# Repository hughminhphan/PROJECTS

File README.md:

# PROJECTS
 My PCB files for my projects

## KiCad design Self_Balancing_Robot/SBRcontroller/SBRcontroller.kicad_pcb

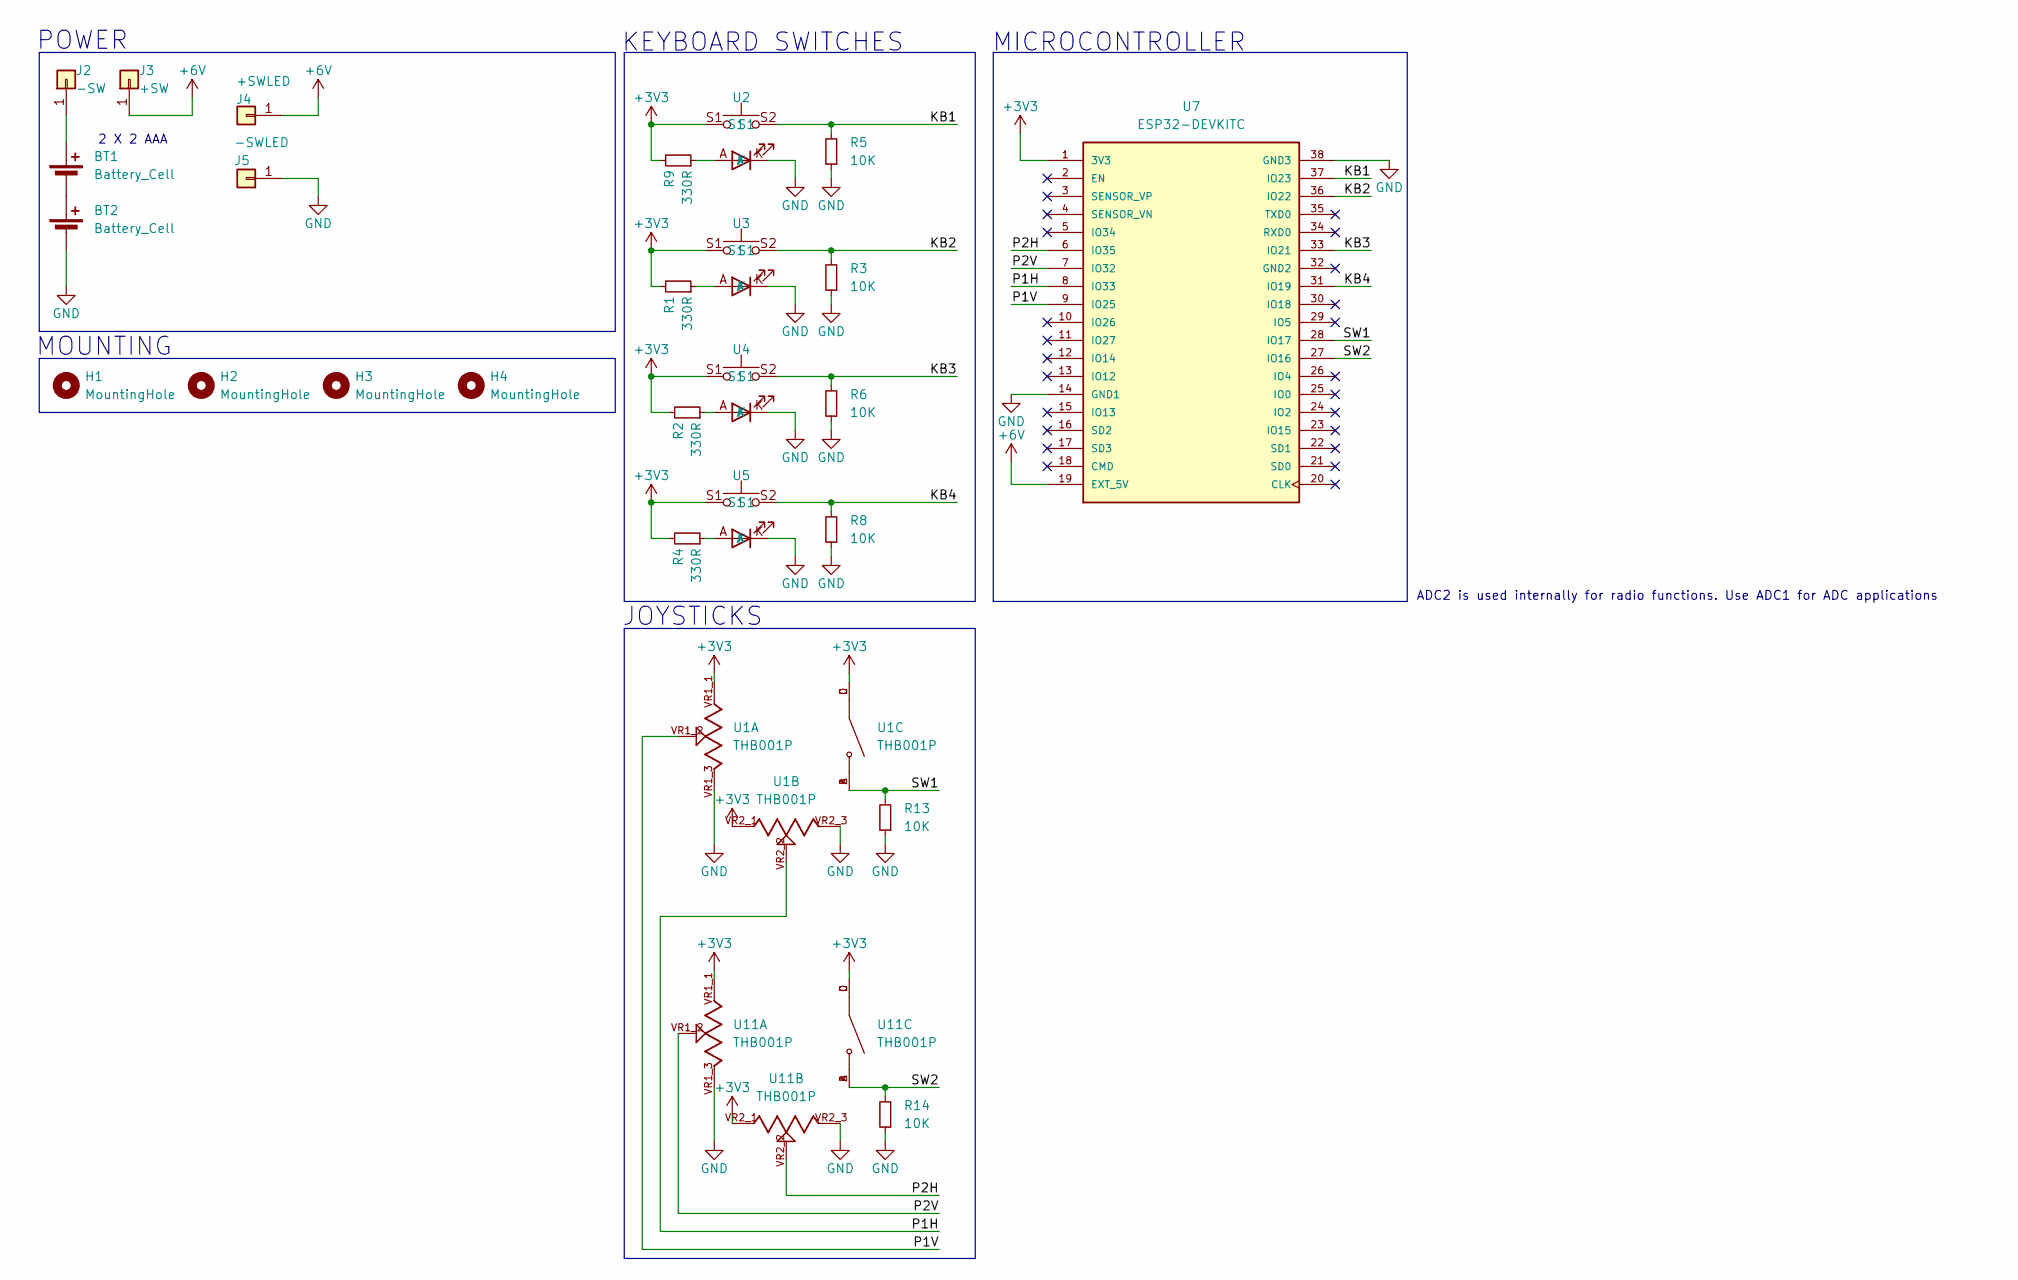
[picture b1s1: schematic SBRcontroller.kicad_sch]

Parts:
BT1, BT2: Battery_Cell; BatteryHolder_Keystone_2468_2xAAA
H1, H2, H3, H4: MountingHole; MountingHole_2.2mm_M2
J2: -SW; SolderWire-1.5sqmm_1x01_D1.7mm_OD3mm
J3: +SW; SolderWire-1.5sqmm_1x01_D1.7mm_OD3mm
J4: +SWLED; SolderWire-1.5sqmm_1x01_D1.7mm_OD3mm
J5: -SWLED; SolderWire-1.5sqmm_1x01_D1.7mm_OD3mm
R1, R2, R4, R9: 330R; R_0805_2012Metric
R3, R5, R6, R8, R13, R14: 10K; R_0805_2012Metric
U1, U11: THB001P; CNK_THB001P; PARTREV 27 Jan 22
U2, U3, U4, U5: Cherry_MX_3mmLED
U7: ESP32-DEVKITC; MODULE_ESP32-DEVKITC; PARTREV N/A

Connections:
+3V3: R1.2, R2.2, R4.2, R9.2, U1.C, U1.D, U1.VR1_1, U1.VR2_1, U2.S1, U3.S1, U4.S1, U5.S1, U7.1 (3V3), U11.C, U11.D, U11.VR1_1, U11.VR2_1
+6V: J3.1, J4.1, U7.19 (EXT_5V)
/KB1: R5.2, U2.S2 (S1), U7.37 (IO23)
/KB2: R3.2, U3.S2 (S1), U7.36 (IO22)
/KB3: R6.2, U4.S2 (S1), U7.33 (IO21)
/KB4: R8.2, U5.S2 (S1), U7.31 (IO19)
/P1H: U1.VR2_2, U7.8 (IO33)
/P1V: U1.VR1_2, U7.9 (IO25)
/P2H: U7.6 (IO35), U11.VR2_2
/P2V: U7.7 (IO32), U11.VR1_2
/SW1: R13.2, U1.A, U1.B, U7.28 (IO17)
/SW2: R14.2, U7.27 (IO16), U11.A, U11.B
GND: BT2.2 (-), J5.1, R3.1, R5.1, R6.1, R8.1, R13.1, R14.1, U1.VR1_3, U1.VR2_3, U2.K, U3.K, U4.K, U5.K, U7.14 (GND1), U7.38 (GND3), U11.VR1_3, U11.VR2_3
unnamed: BT1.1 (+), J2.1
unnamed: BT1.2 (-), BT2.1 (+)
unnamed: R1.1, U3.A
unnamed: R2.1, U4.A
unnamed: R4.1, U5.A
unnamed: R9.1, U2.A

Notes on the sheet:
MICROCONTROLLER
POWER
ADC2 is used internally for radio functions. Use ADC1 for ADC applications
KEYBOARD SWITCHES
JOYSTICKS
2 X 2 AAA
MOUNTING

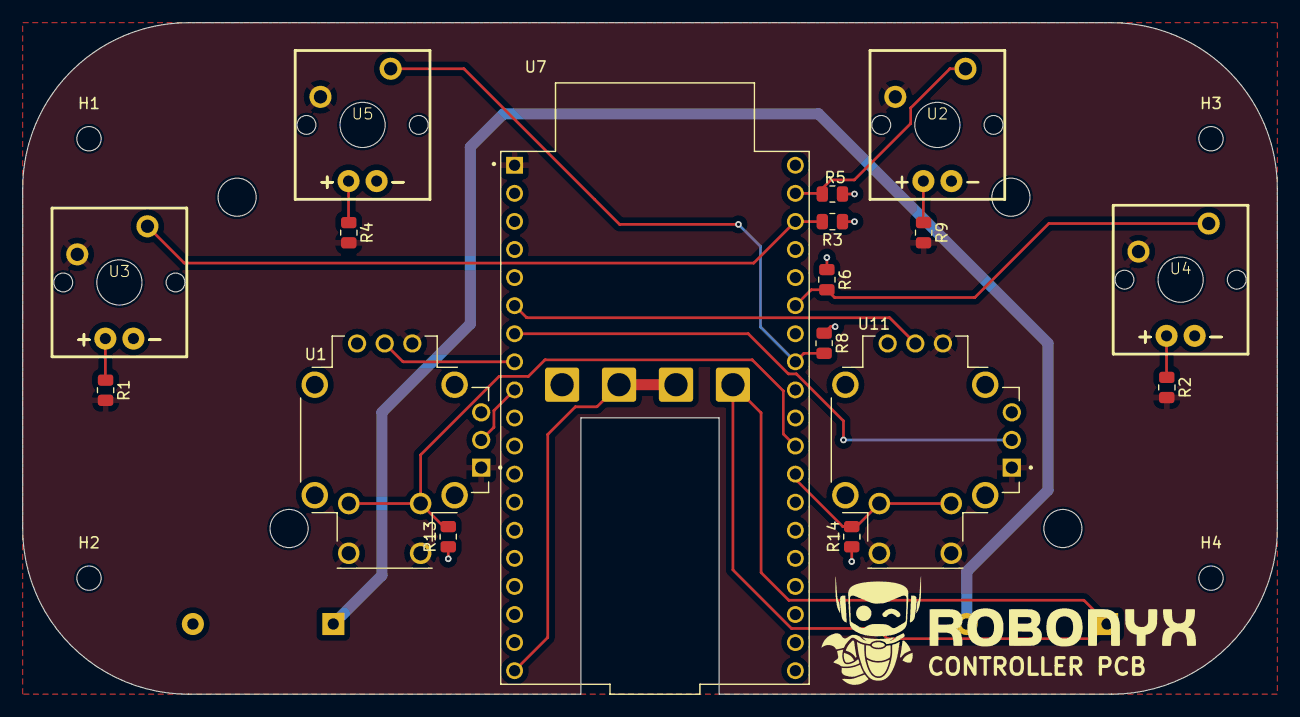
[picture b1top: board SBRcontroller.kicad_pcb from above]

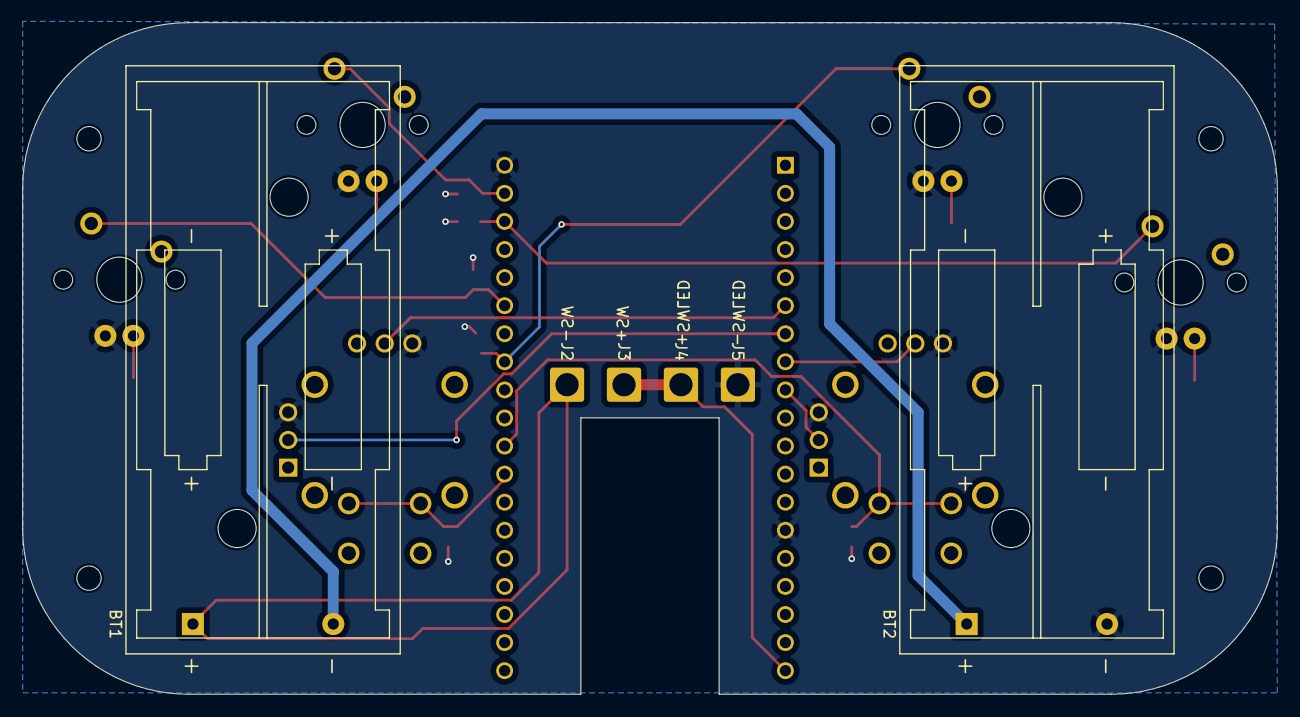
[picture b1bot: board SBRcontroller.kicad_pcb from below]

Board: 2 copper layers, 113.5 x 60.8 mm, 27 parts (6 on the bottom side), 19 nets.

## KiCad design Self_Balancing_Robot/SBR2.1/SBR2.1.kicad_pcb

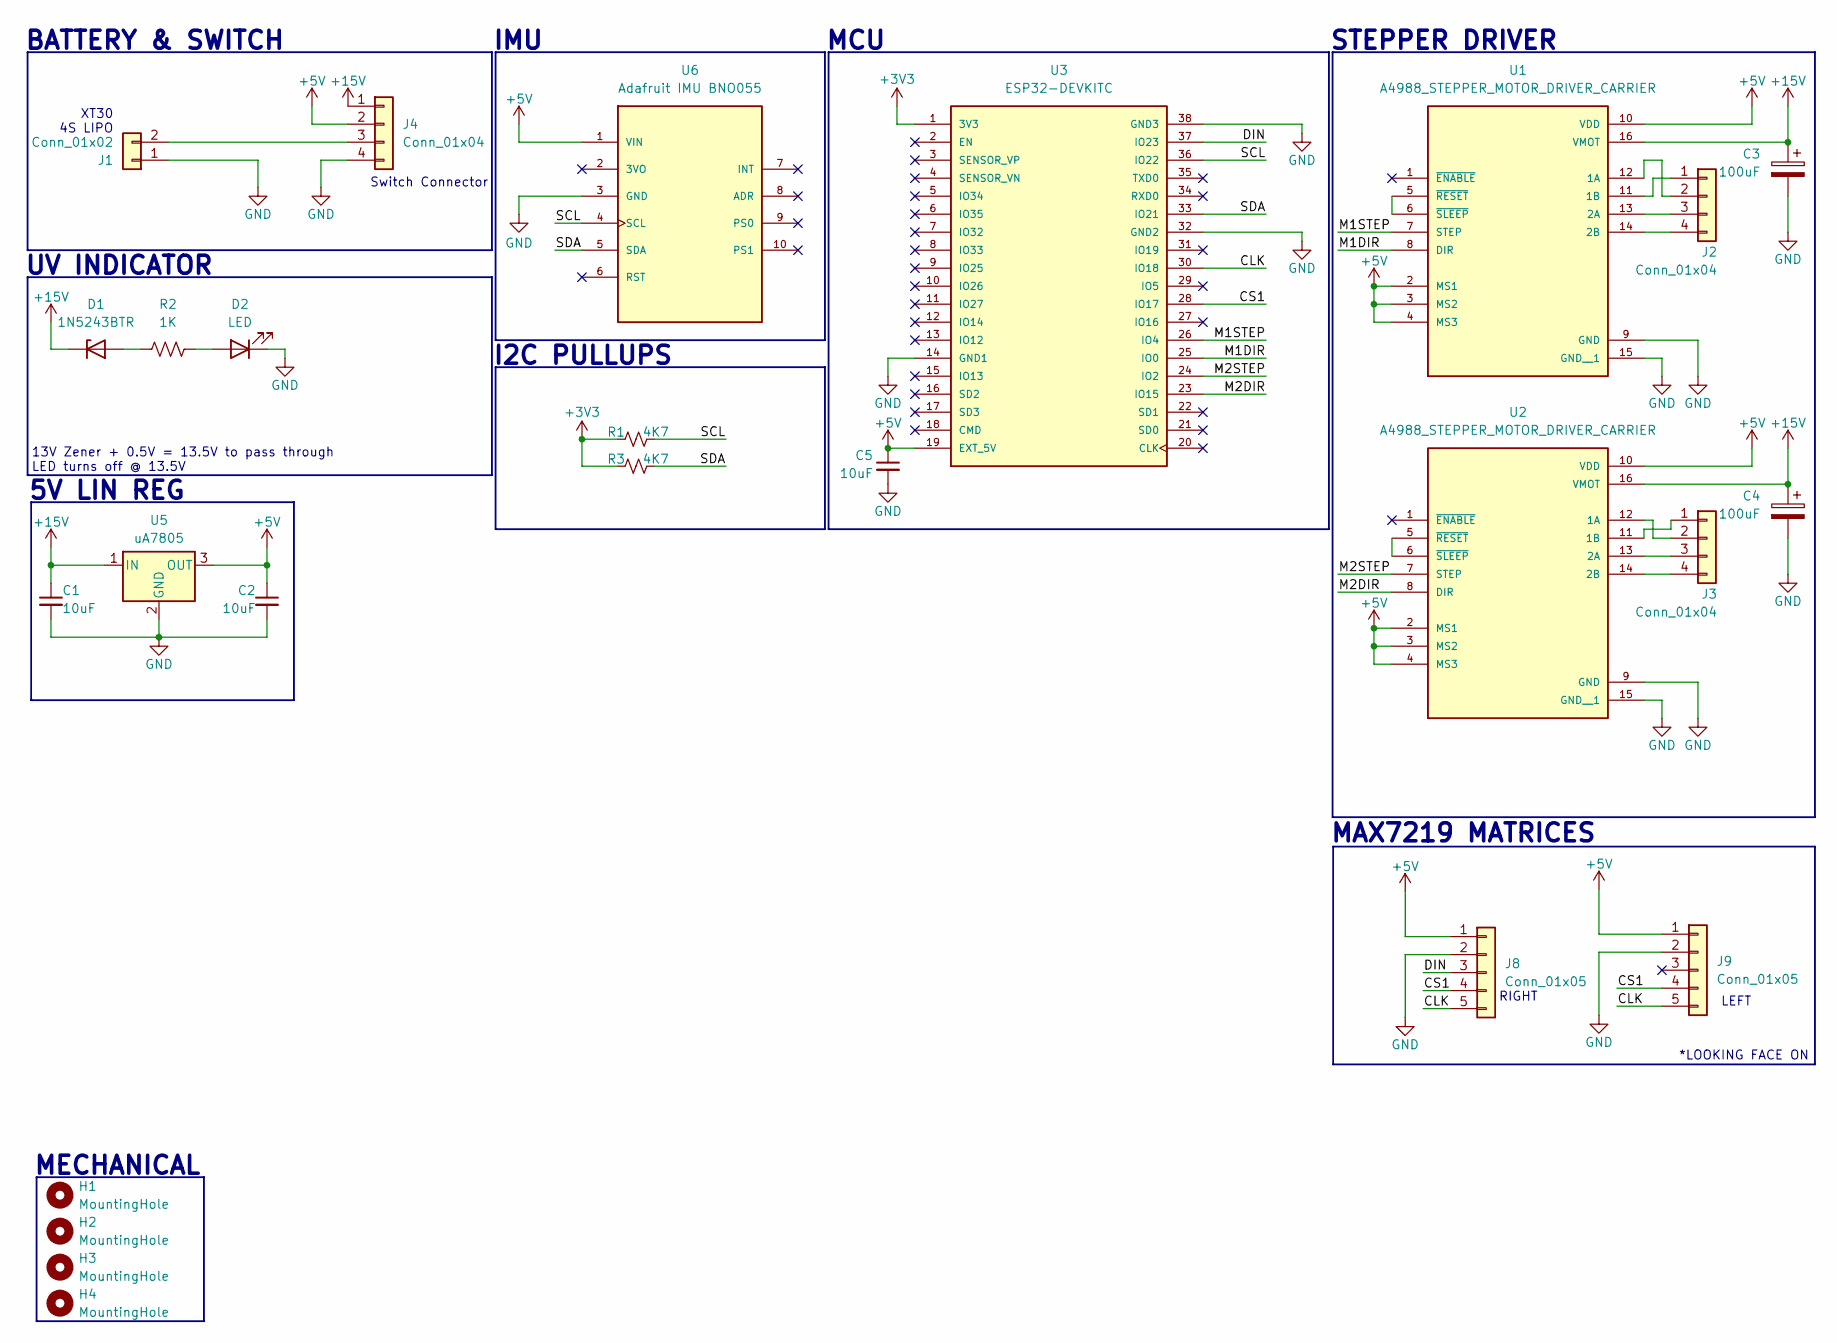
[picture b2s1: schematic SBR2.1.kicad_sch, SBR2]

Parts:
C1, C2, C5: 10uF; C_0805_2012Metric
C3, C4: 100uF; CP_Radial_D6.3mm_P2.50mm
D1: 1N5243BTR; D_DO-35_SOD27_P10.16mm_Horizontal
D2: LED; LED_D5.0mm
H1, H2, H3, H4: MountingHole; MountingHole_3.2mm_M3
J1: Conn_01x02; AMASS_XT30U-M_1x02_P5.0mm_Vertical
J2, J3, J4: Conn_01x04; JST_XH_B4B-XH-AM_1x04_P2.50mm_Vertical
J8, J9: Conn_01x05; PinSocket_1x05_P2.54mm_Vertical
R1, R3: 4K7; R_0805_2012Metric
R2: 1K; R_0805_2012Metric
U1, U2: A4988_STEPPER_MOTOR_DRIVER_CARRIER; MODULE_A4988_STEPPER_MOTOR_DRIVER_CARRIER
U3: ESP32-DEVKITC; MODULE_ESP32-DEVKITC; PARTREV N/A
U5: uA7805; TO-263-3_TabPin2
U6: Adafruit IMU BNO055; PARTREV 2021-03-16

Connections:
+3V3: R1.2, R3.2, U3.1 (3V3)
+5V: C2.1, C5.1, J4.2, J8.1, J9.1, U1.2 (MS1), U1.3 (MS2), U1.4 (MS3), U1.10 (VDD), U2.2 (MS1), U2.3 (MS2), U2.4 (MS3), U2.10 (VDD), U3.19 (EXT_5V), U5.3 (OUT), U6.1 (VIN)
+15V: C1.1, C3.1, C4.1, D1.1 (K), J4.1, U1.16 (VMOT), U2.16 (VMOT), U5.1 (IN)
/CLK: J8.5, J9.5, U3.30 (IO18)
/CS1: J8.4, J9.4, U3.28 (IO17)
/DIN: J8.3, U3.37 (IO23)
/M1DIR: U1.8 (DIR), U3.25 (IO0)
/M1STEP: U1.7 (STEP), U3.26 (IO4)
/M2DIR: U2.8 (DIR), U3.23 (IO15)
/M2STEP: U2.7 (STEP), U3.24 (IO2)
/SCL: R1.1, U3.36 (IO22), U6.4 (SCL)
/SDA: R3.1, U3.33 (IO21), U6.5 (SDA)
GND: C1.2, C2.2, C3.2, C4.2, C5.2, D2.1 (K), J1.1, J4.4, J8.2, J9.2, U1.9 (GND), U1.15 (GND__1), U2.9 (GND), U2.15 (GND__1), U3.14 (GND1), U3.32 (GND2), U3.38 (GND3), U5.2 (GND), U6.3 (GND)
unnamed: D1.2 (A), R2.2
unnamed: D2.2 (A), R2.1
unnamed: J1.2, J4.3
unnamed: J2.1, U1.11 (1B)
unnamed: J2.2, U1.12 (1A)
unnamed: J2.3, U1.13 (2A)
unnamed: J2.4, U1.14 (2B)
unnamed: J3.1, U2.11 (1B)
unnamed: J3.2, U2.12 (1A)
unnamed: J3.3, U2.13 (2A)
unnamed: J3.4, U2.14 (2B)
unnamed: U1.5 (~RESET), U1.6 (~SLEEP)
unnamed: U2.5 (~RESET), U2.6 (~SLEEP)

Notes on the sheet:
MECHANICAL
LEFT
MAX7219 MATRICES
BATTERY & SWITCH
5V LIN REG
UV INDICATOR
RIGHT
I2C PULLUPS
*LOOKING FACE ON
MCU
Switch Connector
13V Zener + 0.5V = 13.5V to pass through LED turns off @ 13.5V
IMU
XT30 4S LIPO
STEPPER DRIVER

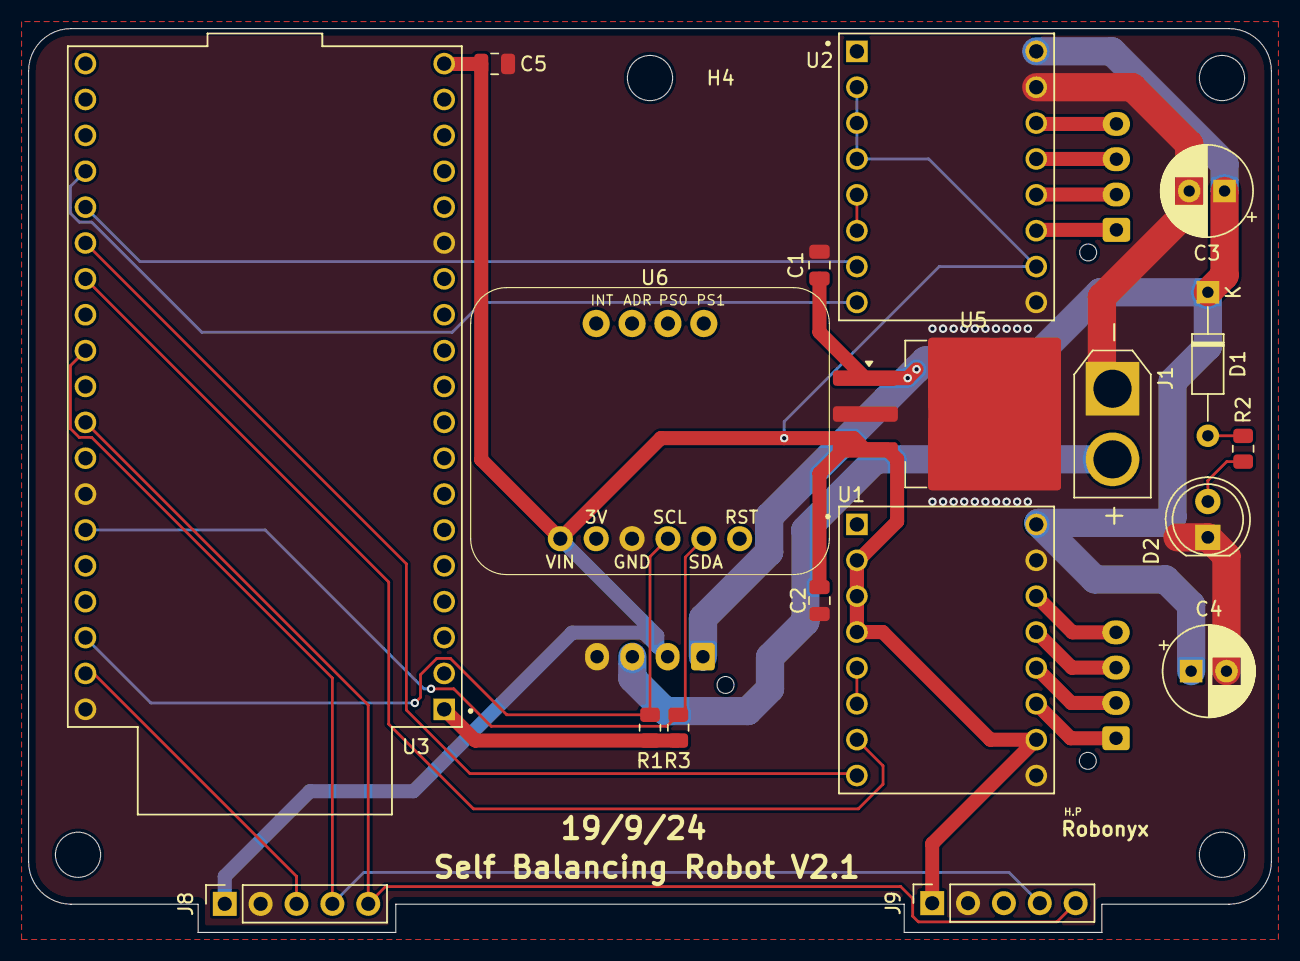
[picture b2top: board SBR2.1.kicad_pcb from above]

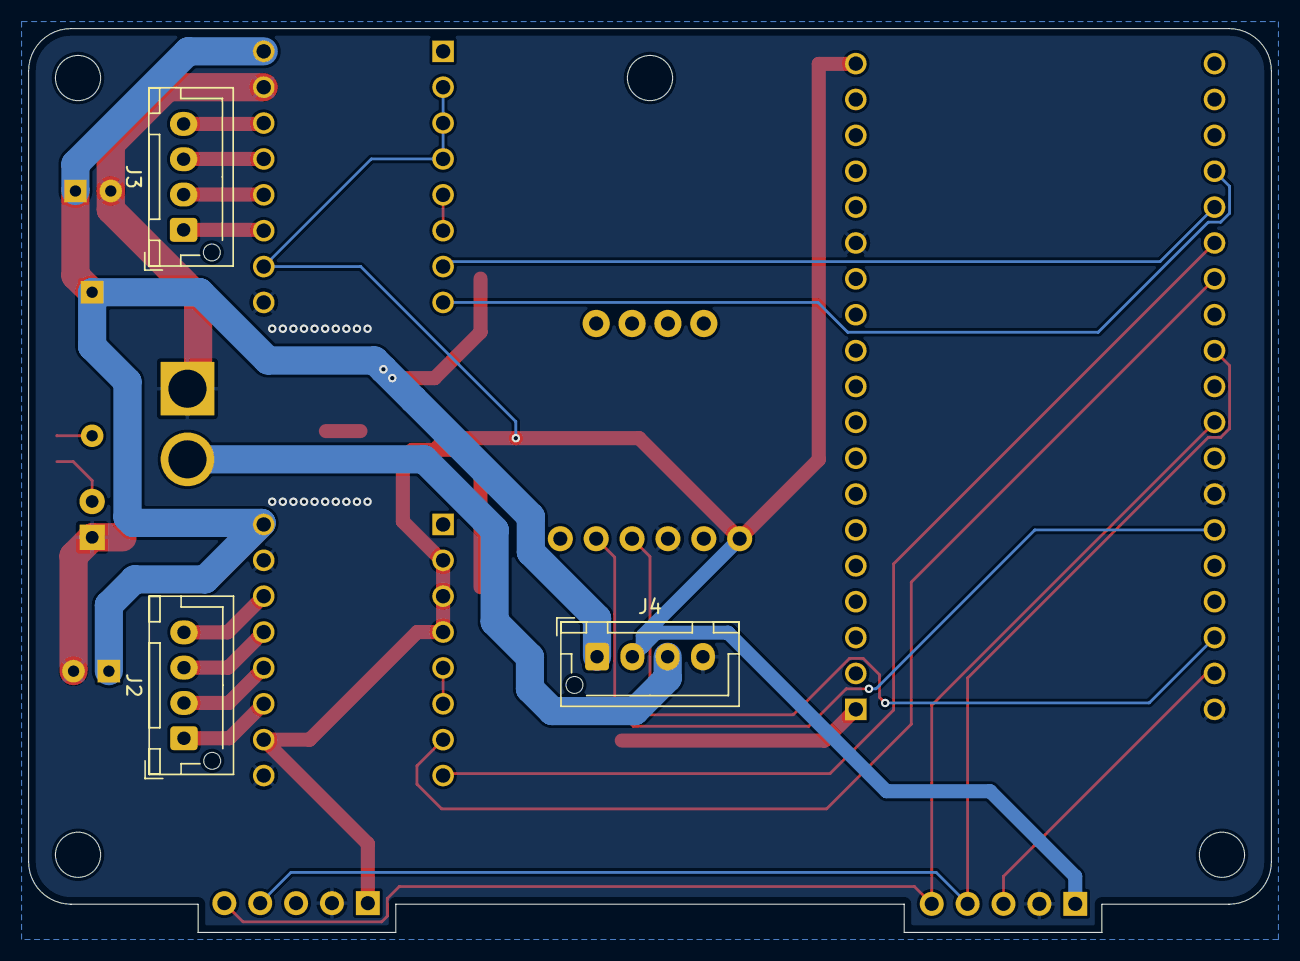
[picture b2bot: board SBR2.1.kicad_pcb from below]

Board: 2 copper layers, 88.0 x 64.0 mm, 25 parts (3 on the bottom side), 26 nets.

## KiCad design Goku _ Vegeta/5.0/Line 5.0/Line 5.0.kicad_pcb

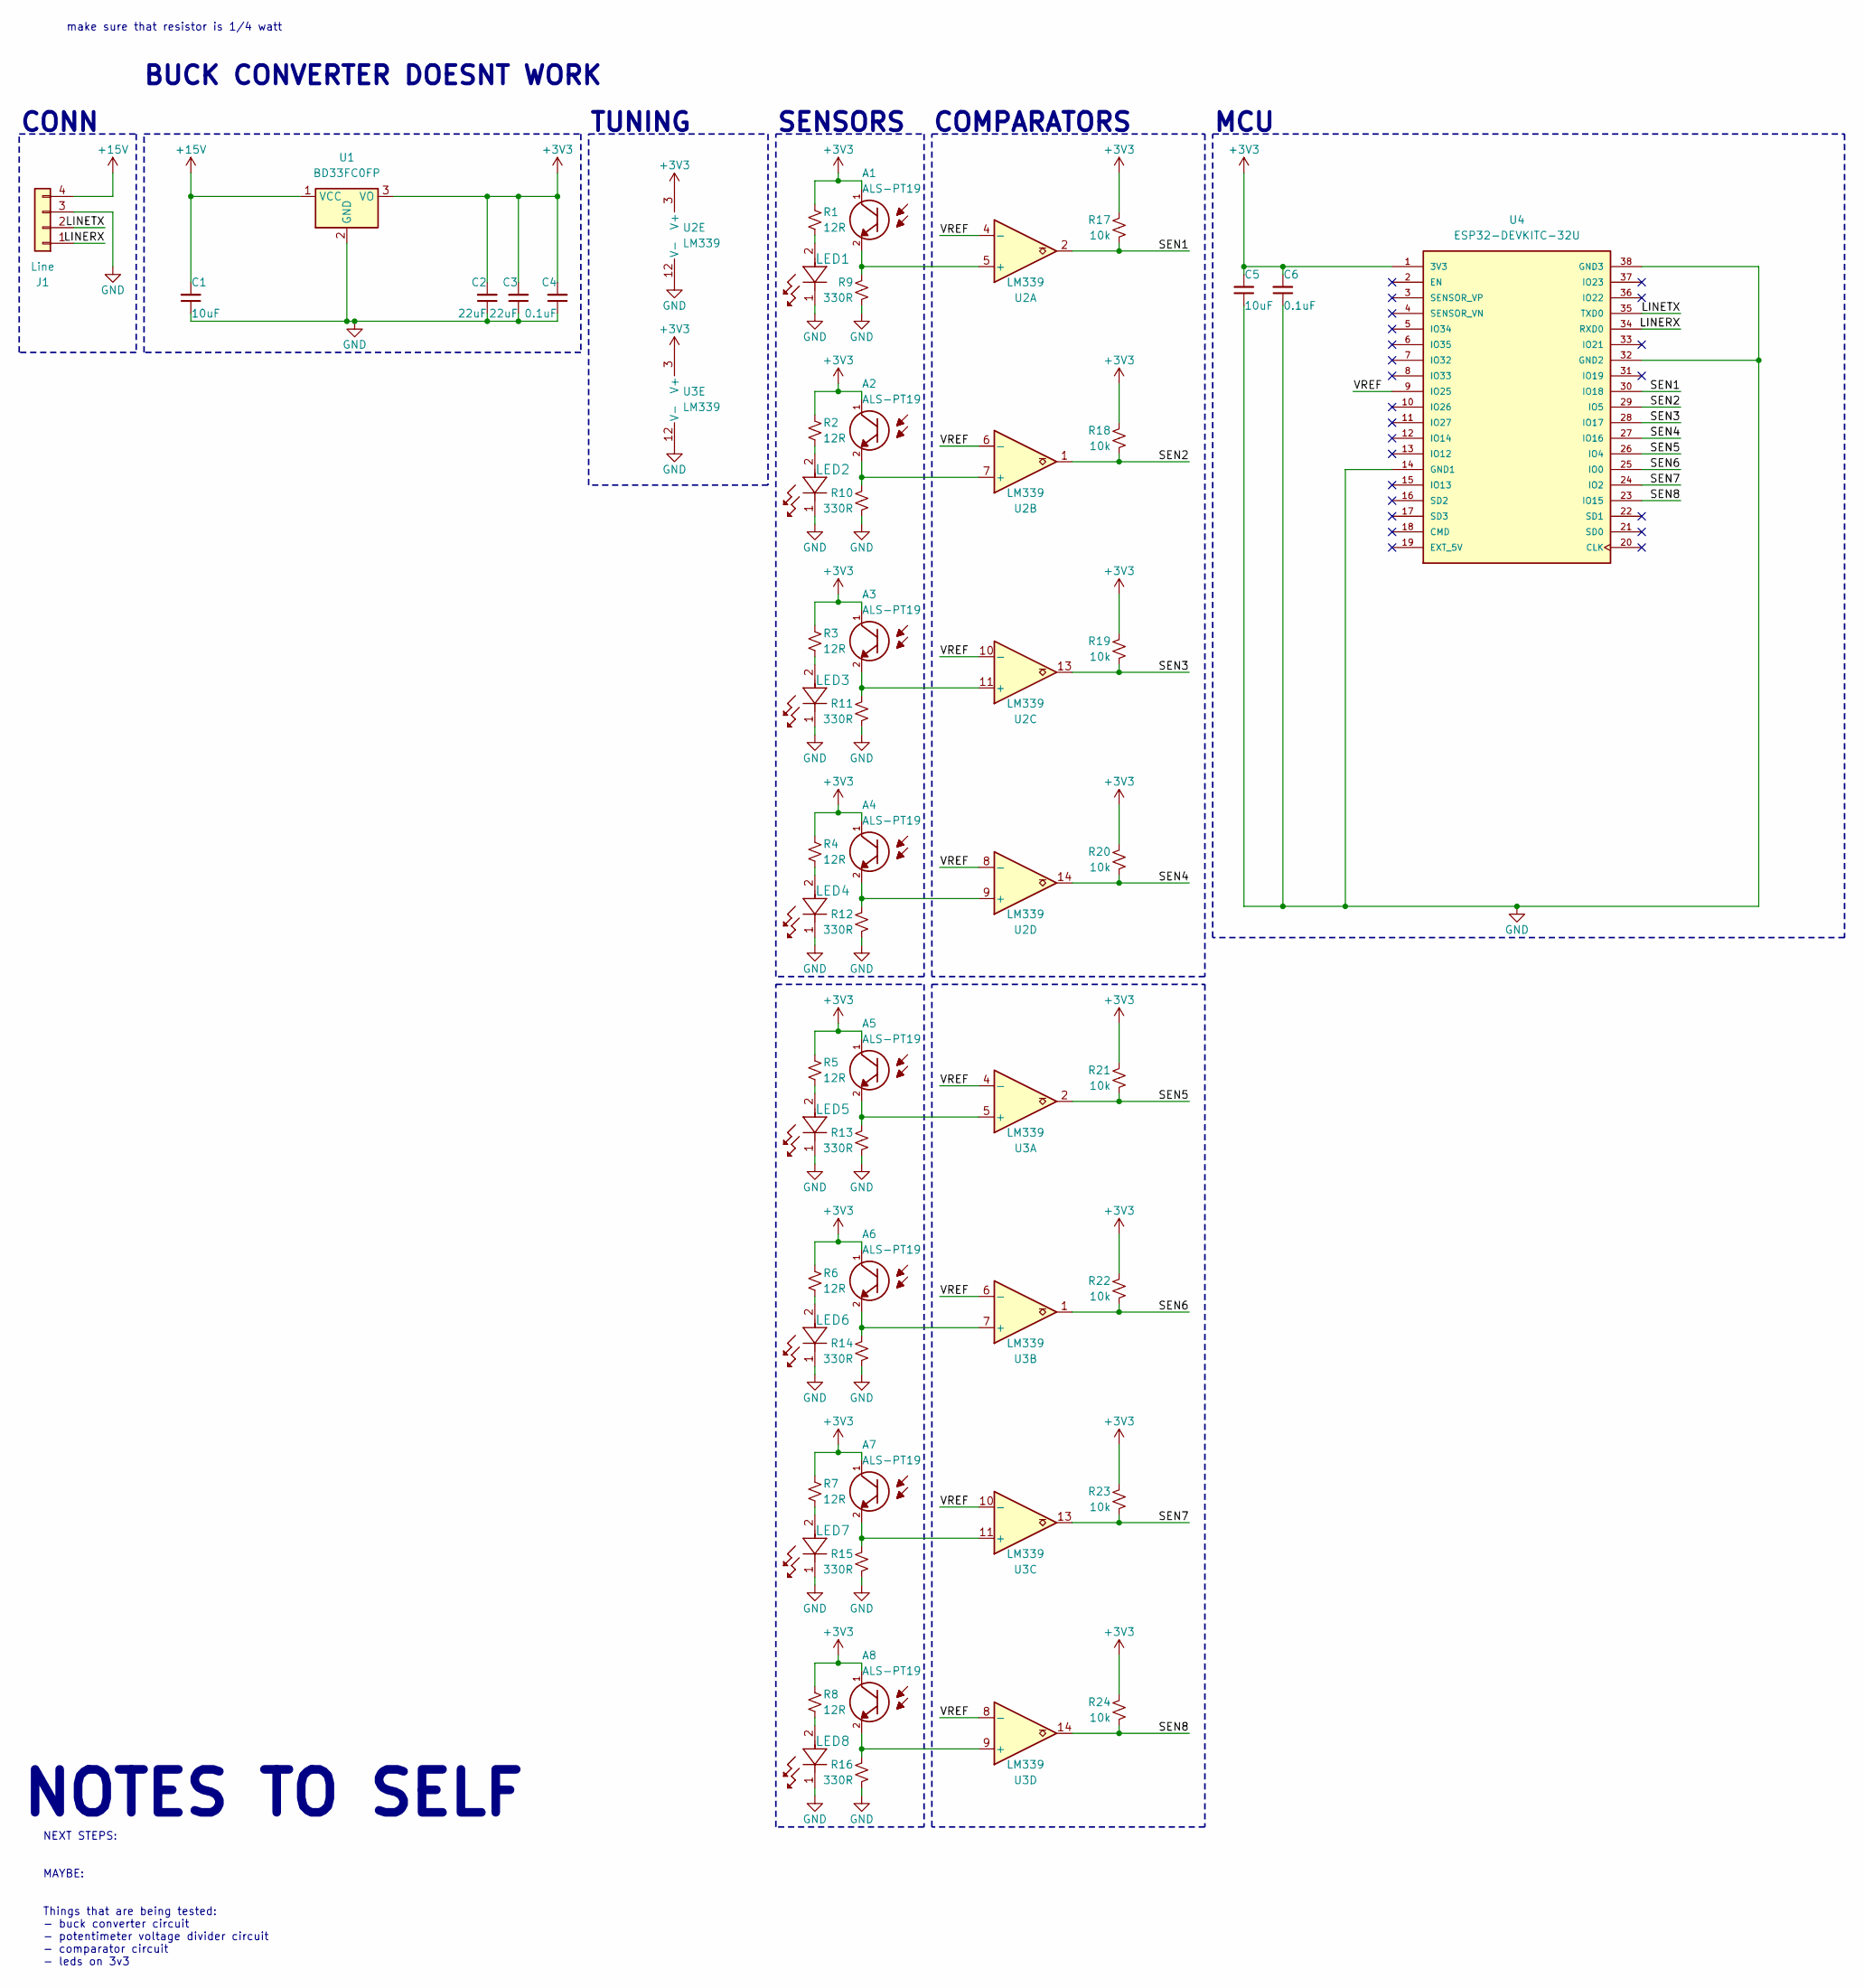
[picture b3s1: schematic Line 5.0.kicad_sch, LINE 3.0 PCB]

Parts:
A1, A2, A3, A4, A5, A6, A7, A8: ALS-PT19; XDCR_ALS-PT19-315C_L177_TR8; PARTREV 5
C1, C5: 10uF; C_0805_2012Metric
C2, C3: 22uF; C_0805_2012Metric
C4, C6: 0.1uF; C_0805_2012Metric
J1: Line; JST_XH_B4B-XH-A_1x04_P2.50mm_Vertical
LED1, LED2, LED3, LED4, LED5, LED6, LED7, LED8: JB2835AWT-W-U30GA0000-N0000001; LED_J2835_CRW
R1, R2, R3, R4, R5, R6, R7, R8: 12R; R_0805_2012Metric
R9, R10, R11, R12, R13, R14, R15, R16: 330R; R_0805_2012Metric
R17, R18, R19, R20, R21, R22, R23, R24: 10k; R_0805_2012Metric
U1: BD33FC0FP; TO-252-2
U2, U3: LM339; TSSOP-14_W4.4mm
U4: ESP32-DEVKITC-32U; MODULE_ESP32-DEVKITC-32U; PARTREV N/A

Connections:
+3V3: A1.1, A2.1, A3.1, A4.1, A5.1, A6.1, A7.1, A8.1, C2.2, C3.2, C4.2, C5.2, C6.2, R1.1, R2.1, R3.1, R4.1, R5.1, R6.1, R7.1, R8.1, R17.2, R18.2, R19.2, R20.2, R21.2, R22.2, R23.2, R24.2, U1.3 (VO), U2.3 (V+), U3.3 (V+), U4.1 (3V3)
+15V: C1.2, J1.4, U1.1 (VCC)
/LINERX: J1.1, U4.34 (RXD0)
/LINETX: J1.2, U4.35 (TXD0)
/SEN1: R17.1, U2.2, U4.30 (IO18)
/SEN2: R18.1, U2.1, U4.29 (IO5)
/SEN3: R19.1, U2.13, U4.28 (IO17)
/SEN4: R20.1, U2.14, U4.27 (IO16)
/SEN5: R21.1, U3.2, U4.26 (IO4)
/SEN6: R22.1, U3.1, U4.25 (IO0)
/SEN7: R23.1, U3.13, U4.24 (IO2)
/SEN8: R24.1, U3.14, U4.23 (IO15)
/VREF: U2.4 (-), U2.6 (-), U2.8 (-), U2.10 (-), U3.4 (-), U3.6 (-), U3.8 (-), U3.10 (-), U4.9 (IO25)
GND: C1.1, C2.1, C3.1, C4.1, C5.1, C6.1, J1.3, LED1.1, LED2.1, LED3.1, LED4.1, LED5.1, LED6.1, LED7.1, LED8.1, R9.1, R10.1, R11.1, R12.1, R13.1, R14.1, R15.1, R16.1, U1.2 (GND), U2.12 (V-), U3.12 (V-), U4.14 (GND1), U4.32 (GND2), U4.38 (GND3)
unnamed: LED1.2, R1.2
unnamed: LED2.2, R2.2
unnamed: LED3.2, R3.2
unnamed: LED4.2, R4.2
unnamed: LED5.2, R5.2
unnamed: LED6.2, R6.2
unnamed: LED7.2, R7.2
unnamed: LED8.2, R8.2
unnamed: A1.2, R9.2, U2.5 (+)
unnamed: A2.2, R10.2, U2.7 (+)
unnamed: A3.2, R11.2, U2.11 (+)
unnamed: A4.2, R12.2, U2.9 (+)
unnamed: A5.2, R13.2, U3.5 (+)
unnamed: A6.2, R14.2, U3.7 (+)
unnamed: A7.2, R15.2, U3.11 (+)
unnamed: A8.2, R16.2, U3.9 (+)

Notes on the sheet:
NOTES TO SELF
NEXT STEPS: MAYBE: Things that are being tested: - buck converter circuit - potentimeter voltage divider circuit - comparator circuit - leds on 3v3
SENSORS
TUNING
make sure that resistor is 1/4 watt
CONN
MCU
BUCK CONVERTER DOESNT WORK
COMPARATORS

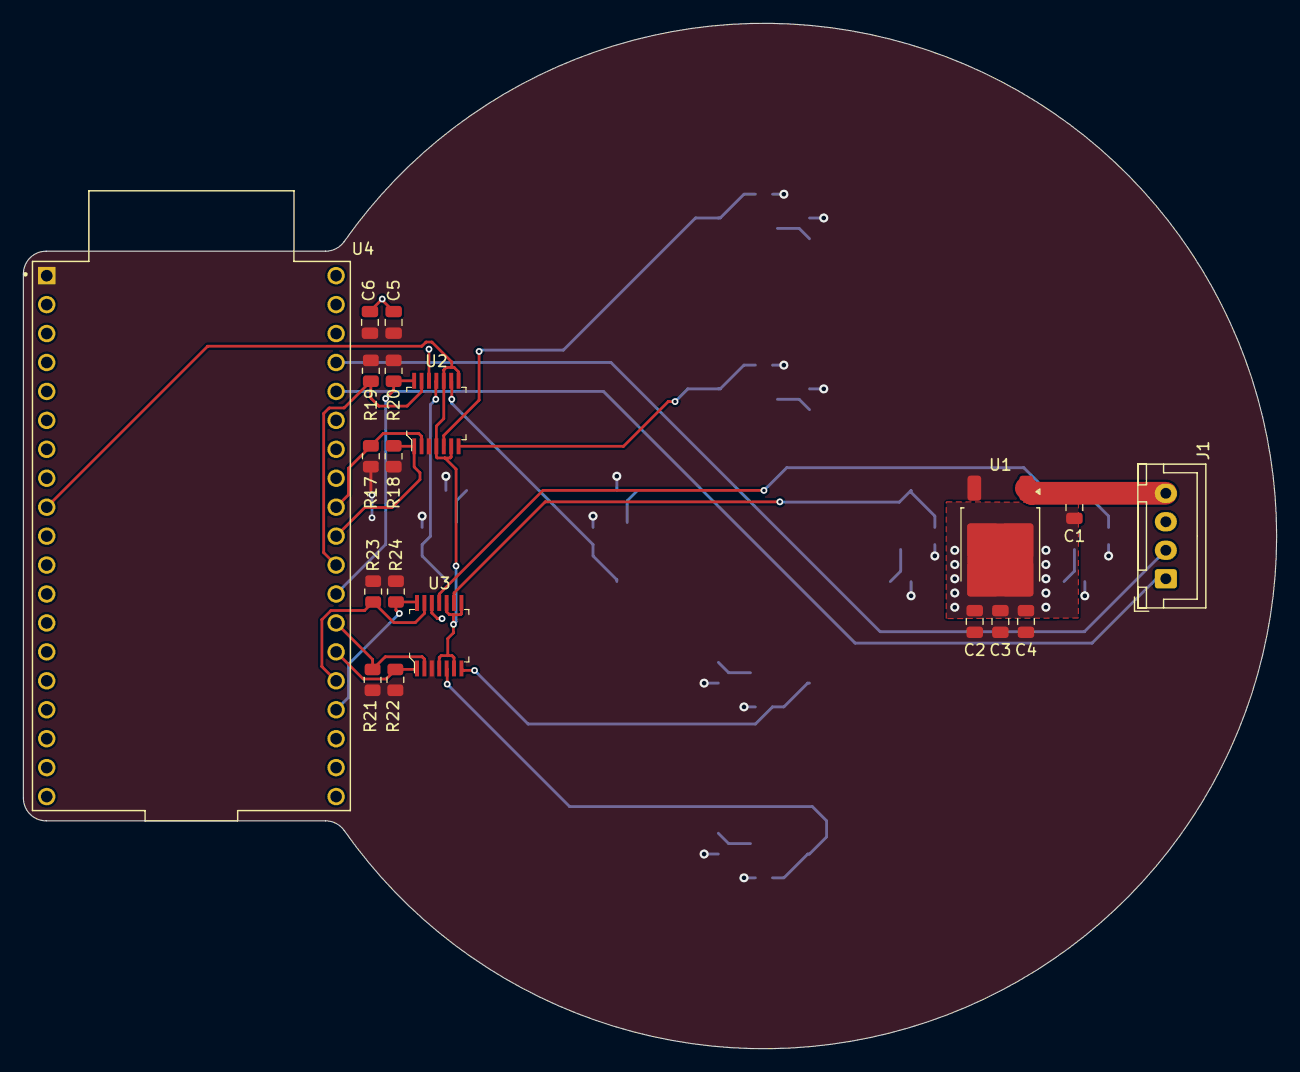
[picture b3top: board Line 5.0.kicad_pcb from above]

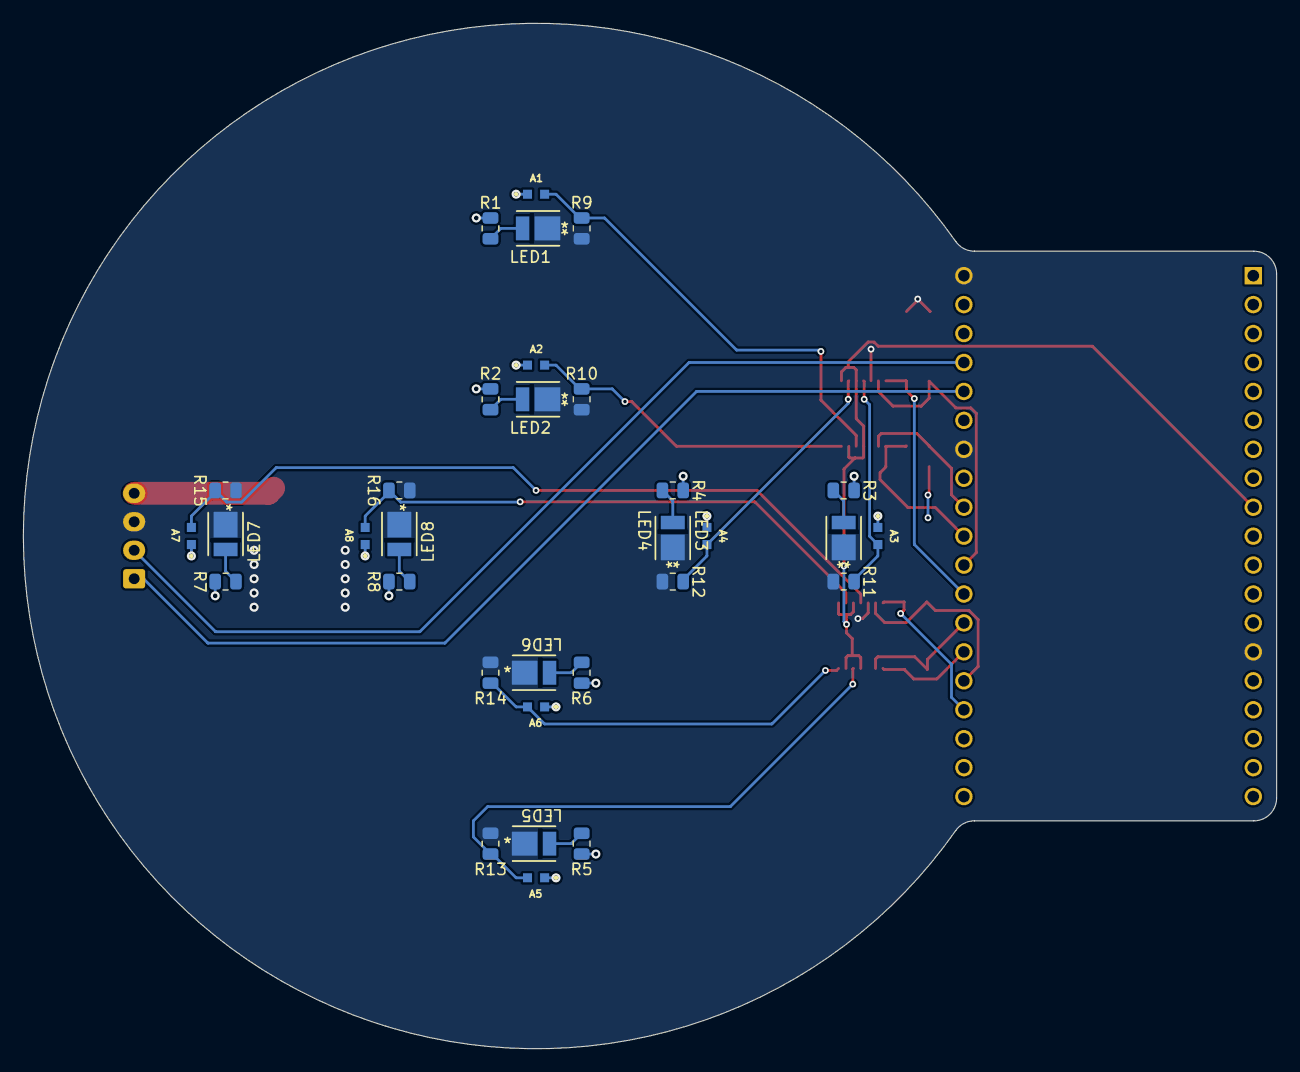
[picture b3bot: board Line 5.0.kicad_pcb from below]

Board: 2 copper layers, 110.0 x 90.0 mm, 51 parts (32 on the bottom side), 30 nets.
